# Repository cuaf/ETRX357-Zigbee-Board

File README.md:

Telegesis ETRX357 Zigbee Breakout
================

This is a breakout for the Telegesis ETRX357 Zigbee board.
Can fit the LRS and HR-LRS variants for use with external antennas and an integrated power amplifier. 

Update 17/11/14 - Boards confirmed working, initial failure must have been poor soldering overheating the board.

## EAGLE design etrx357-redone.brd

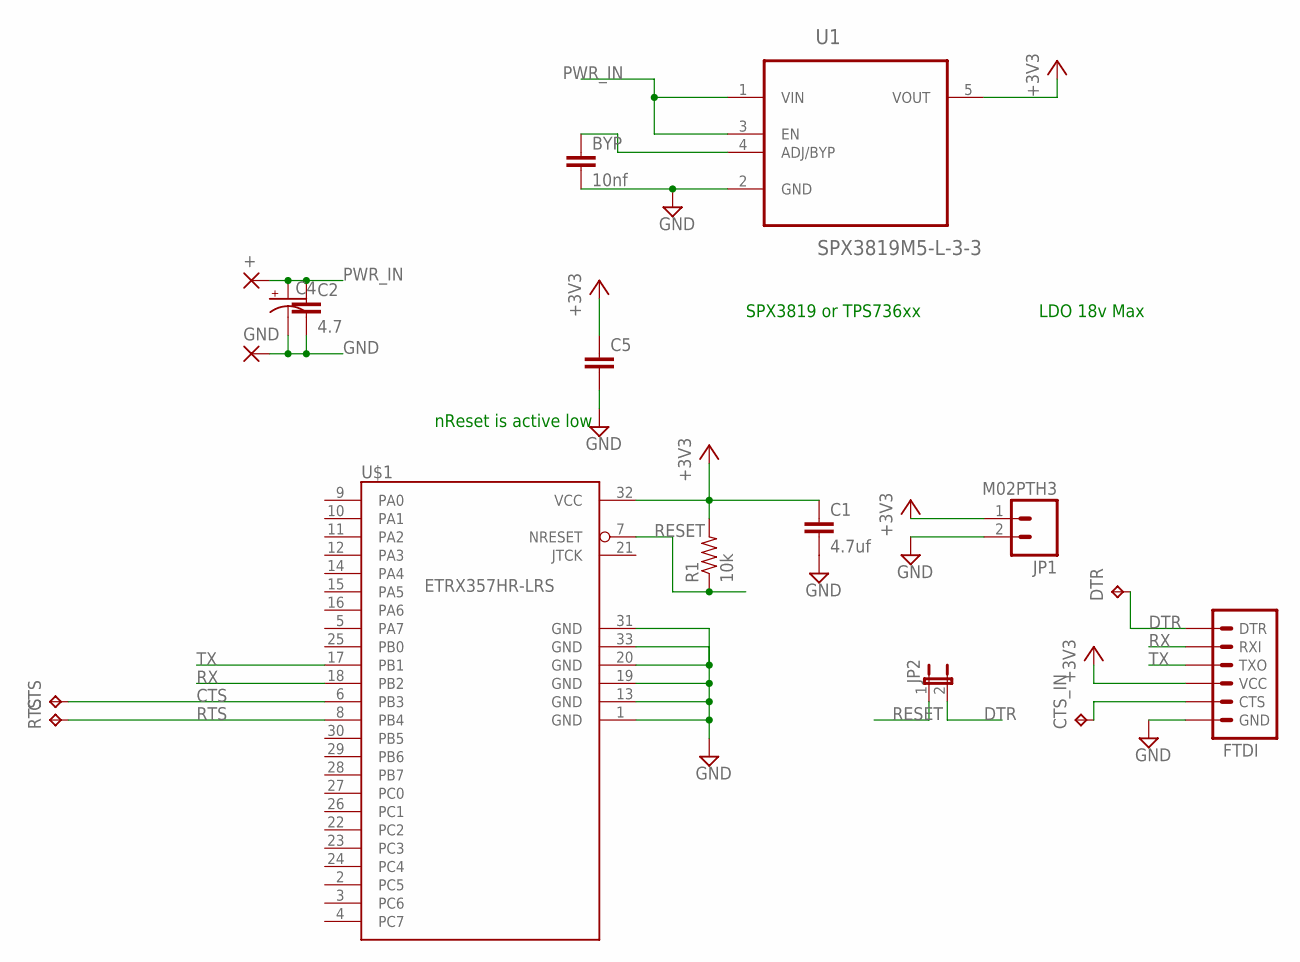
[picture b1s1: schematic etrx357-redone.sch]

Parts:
+: 3,17/1,3
BYP: 10nf; 0603-CAP
C1: 4.7uf; 0603-CAP
C2: 4.7; 0603-CAP
C4: CAP_POLPTH1; CPOL-RADIAL-100UF-25V
C5: CAPPTH; CAP-PTH-SMALL
CTS: TPTP20R; TP20R
CTS_IN: TPTP20R; TP20R
DTR: TPTP20R; TP20R
FTDI: ARDUINO_SERIAL_PROGRAMPTH; 1X06
GND: 3,17/1,3
JP1: M02PTH3; 1X02_LONGPADS
JP2: JUMPER-2-OLDSMD-NO; SJ_2S-NO
R1: 10k; 0603-RES
RTS: TPTP20R; TP20R
U1: SPX3819M5-L-3-3; SOT95P280X145-5N
U$1: ETRX357HR-LRS; ETRX3

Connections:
+3V3: C1.1, C5.1, FTDI.4 (VCC), JP1.1, R1.2, U1.5 (VOUT), U$1.32 (VCC)
CTS: CTS.TP, U$1.6 (PB3)
DTR: DTR.TP, FTDI.1 (DTR), JP2.2
GND: BYP.2, C1.2, C2.2, C4.2 (-), C5.2, FTDI.6 (GND), GND.1, JP1.2, U1.2 (GND), U$1.1 (GND), U$1.13 (GND), U$1.19 (GND), U$1.20 (GND), U$1.31 (GND), U$1.33 (GND)
unnamed: CTS_IN.TP, FTDI.5 (CTS)
unnamed: BYP.1, U1.4 (ADJ/BYP)
PWR_IN: +.1, C2.1, C4.1 (+), U1.1 (VIN), U1.3 (EN)
RESET: JP2.1, R1.1, U$1.7 (NRESET)
RTS: RTS.TP, U$1.8 (PB4)
RX: FTDI.2 (RXI), U$1.18 (PB2)
TX: FTDI.3 (TXO), U$1.17 (PB1)

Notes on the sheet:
nReset is active low
LDO 18v Max
SPX3819 or TPS736xx

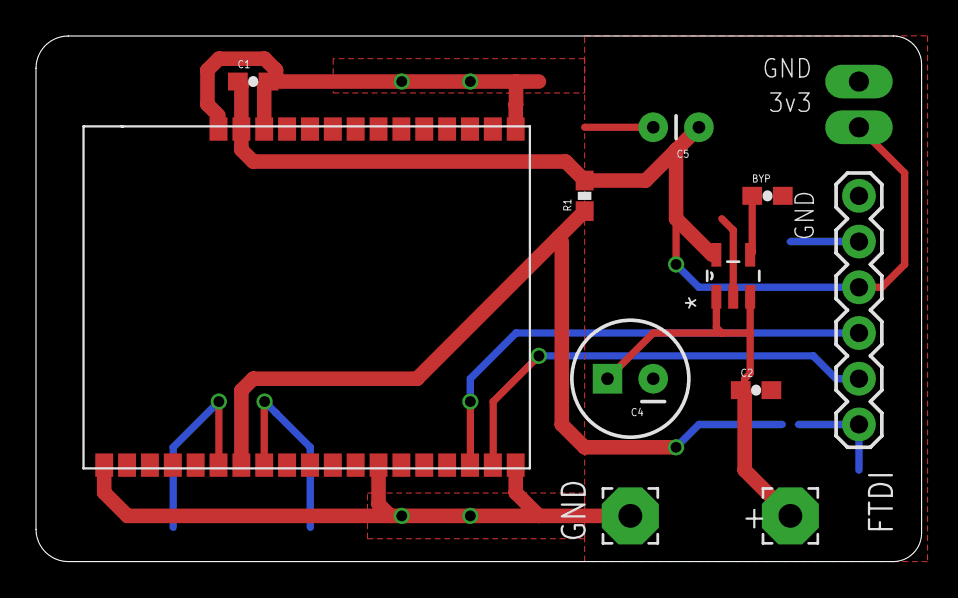
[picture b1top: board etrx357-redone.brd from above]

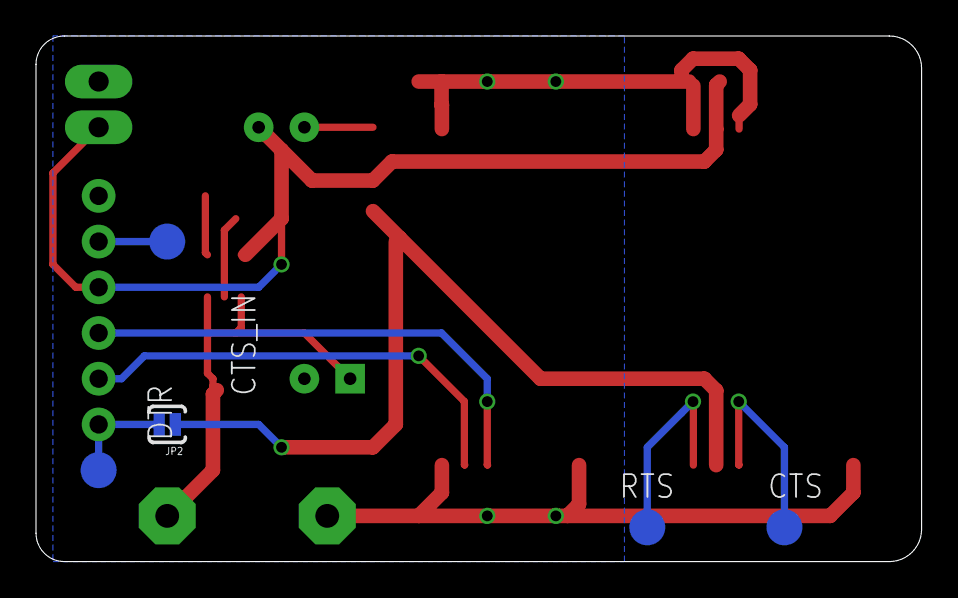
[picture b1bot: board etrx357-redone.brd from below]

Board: 2 copper layers, 49.2 x 29.2 mm, 17 parts (5 on the bottom side), 11 nets.

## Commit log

2014-11-17 first
2014-11-17 Working board assembled

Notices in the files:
parts and their libraries:
SparkFun-Capacitors: Licensing: CC v3.0 Share-Alike You are welcome to use this library for commercial purposes.
